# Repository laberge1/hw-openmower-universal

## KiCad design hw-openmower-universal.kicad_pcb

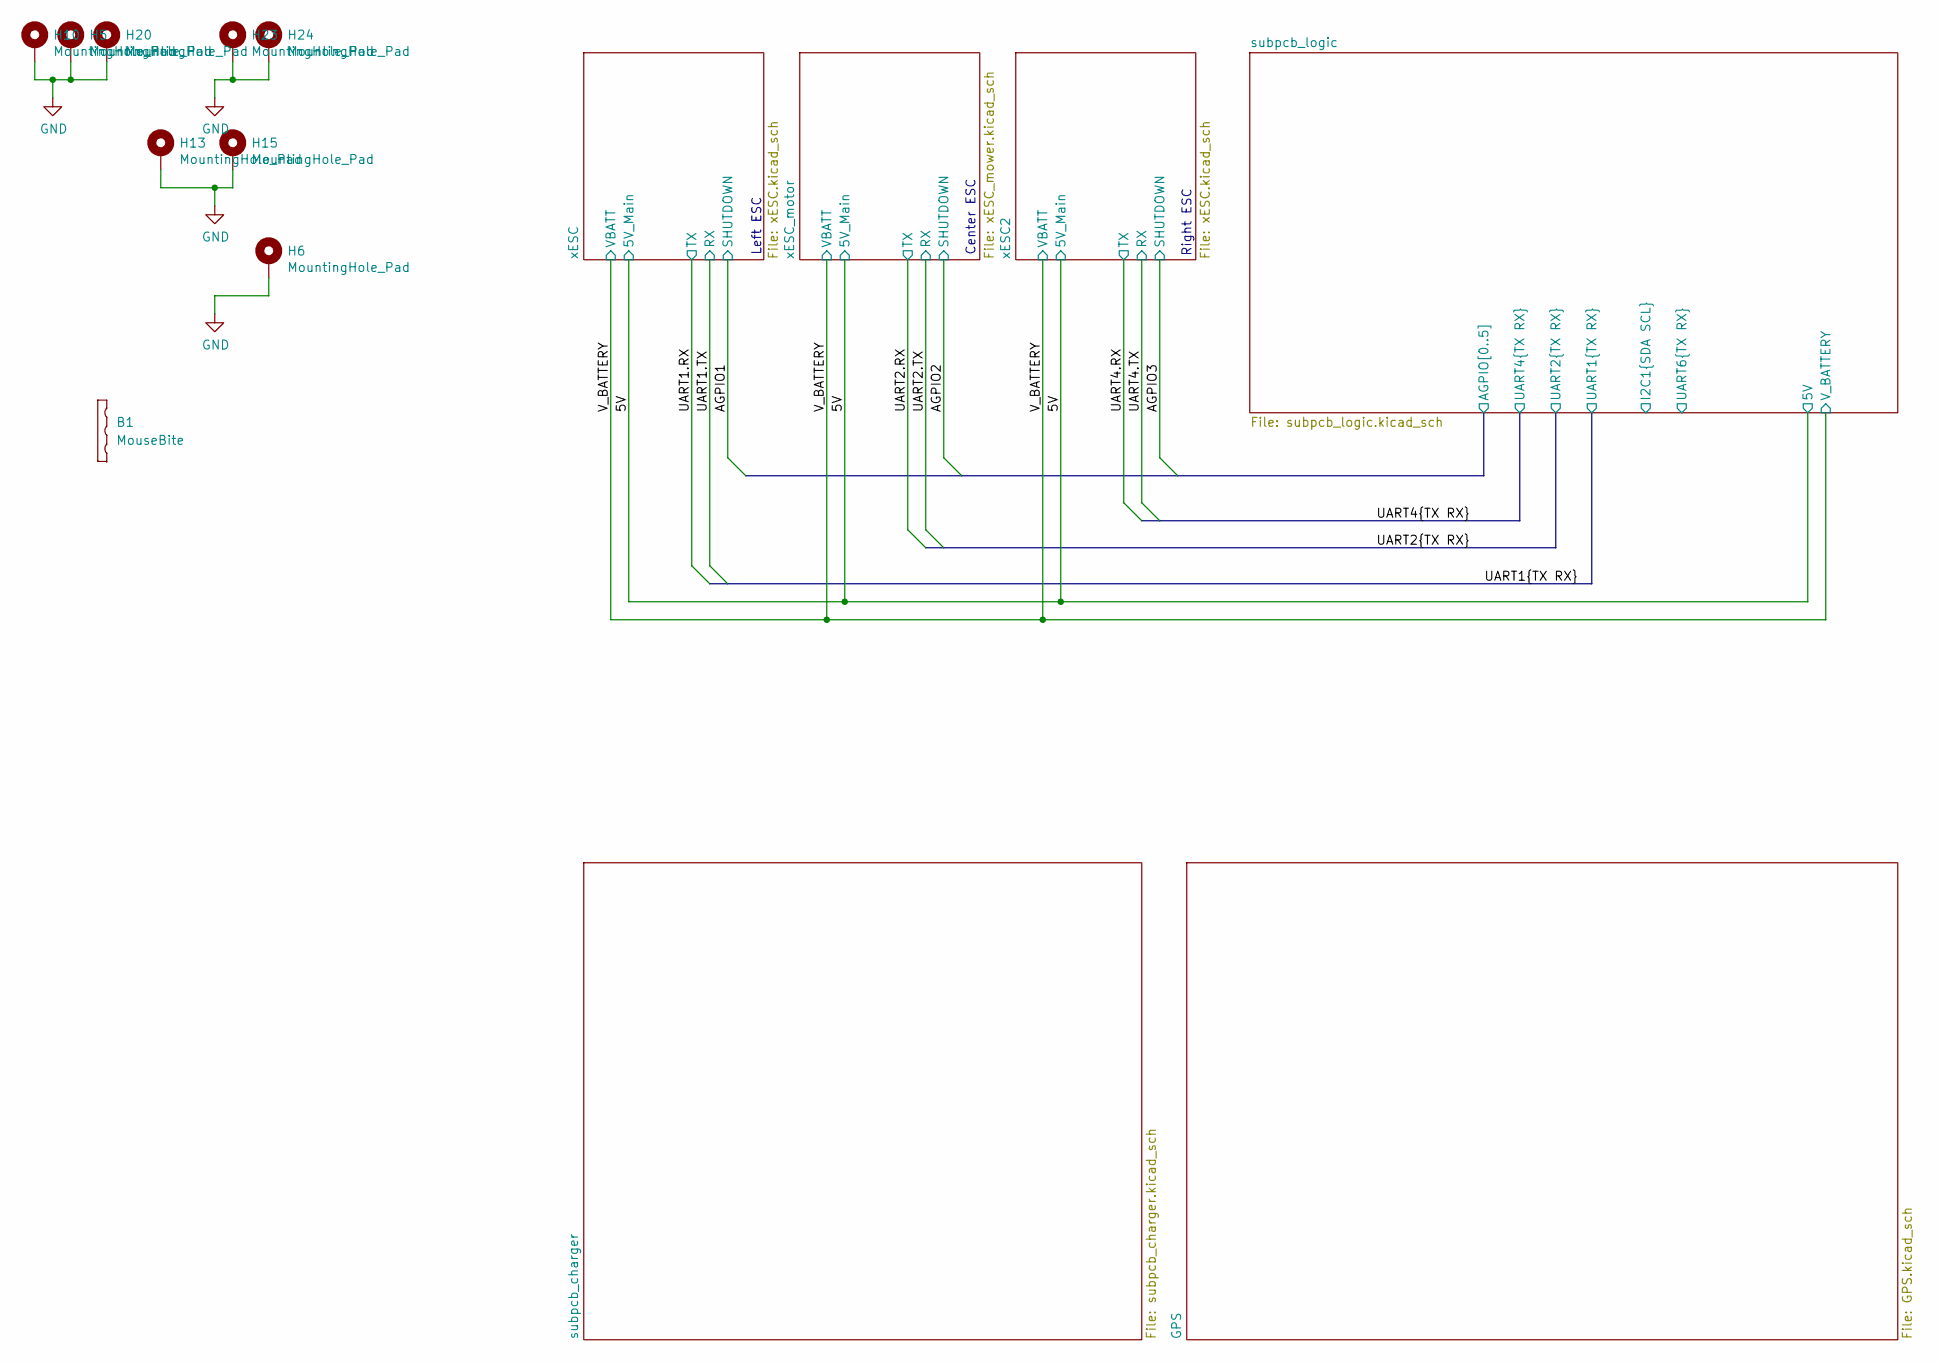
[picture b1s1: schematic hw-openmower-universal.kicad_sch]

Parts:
B1: MouseBite; MouseBite-Slot_2.0x2.0mm_outset_D0.5mm_P0.85mm_3h
H5, H6, H10, H13, H15, H20, H23, H24: MountingHole_Pad; MountingHole_4.3mm_M4_Pad_Via

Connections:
GND: H5.1, H6.1, H10.1, H13.1, H15.1, H20.1, H23.1, H24.1; also elsewhere on the board

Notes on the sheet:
Left ESC
Center ESC
Right ESC

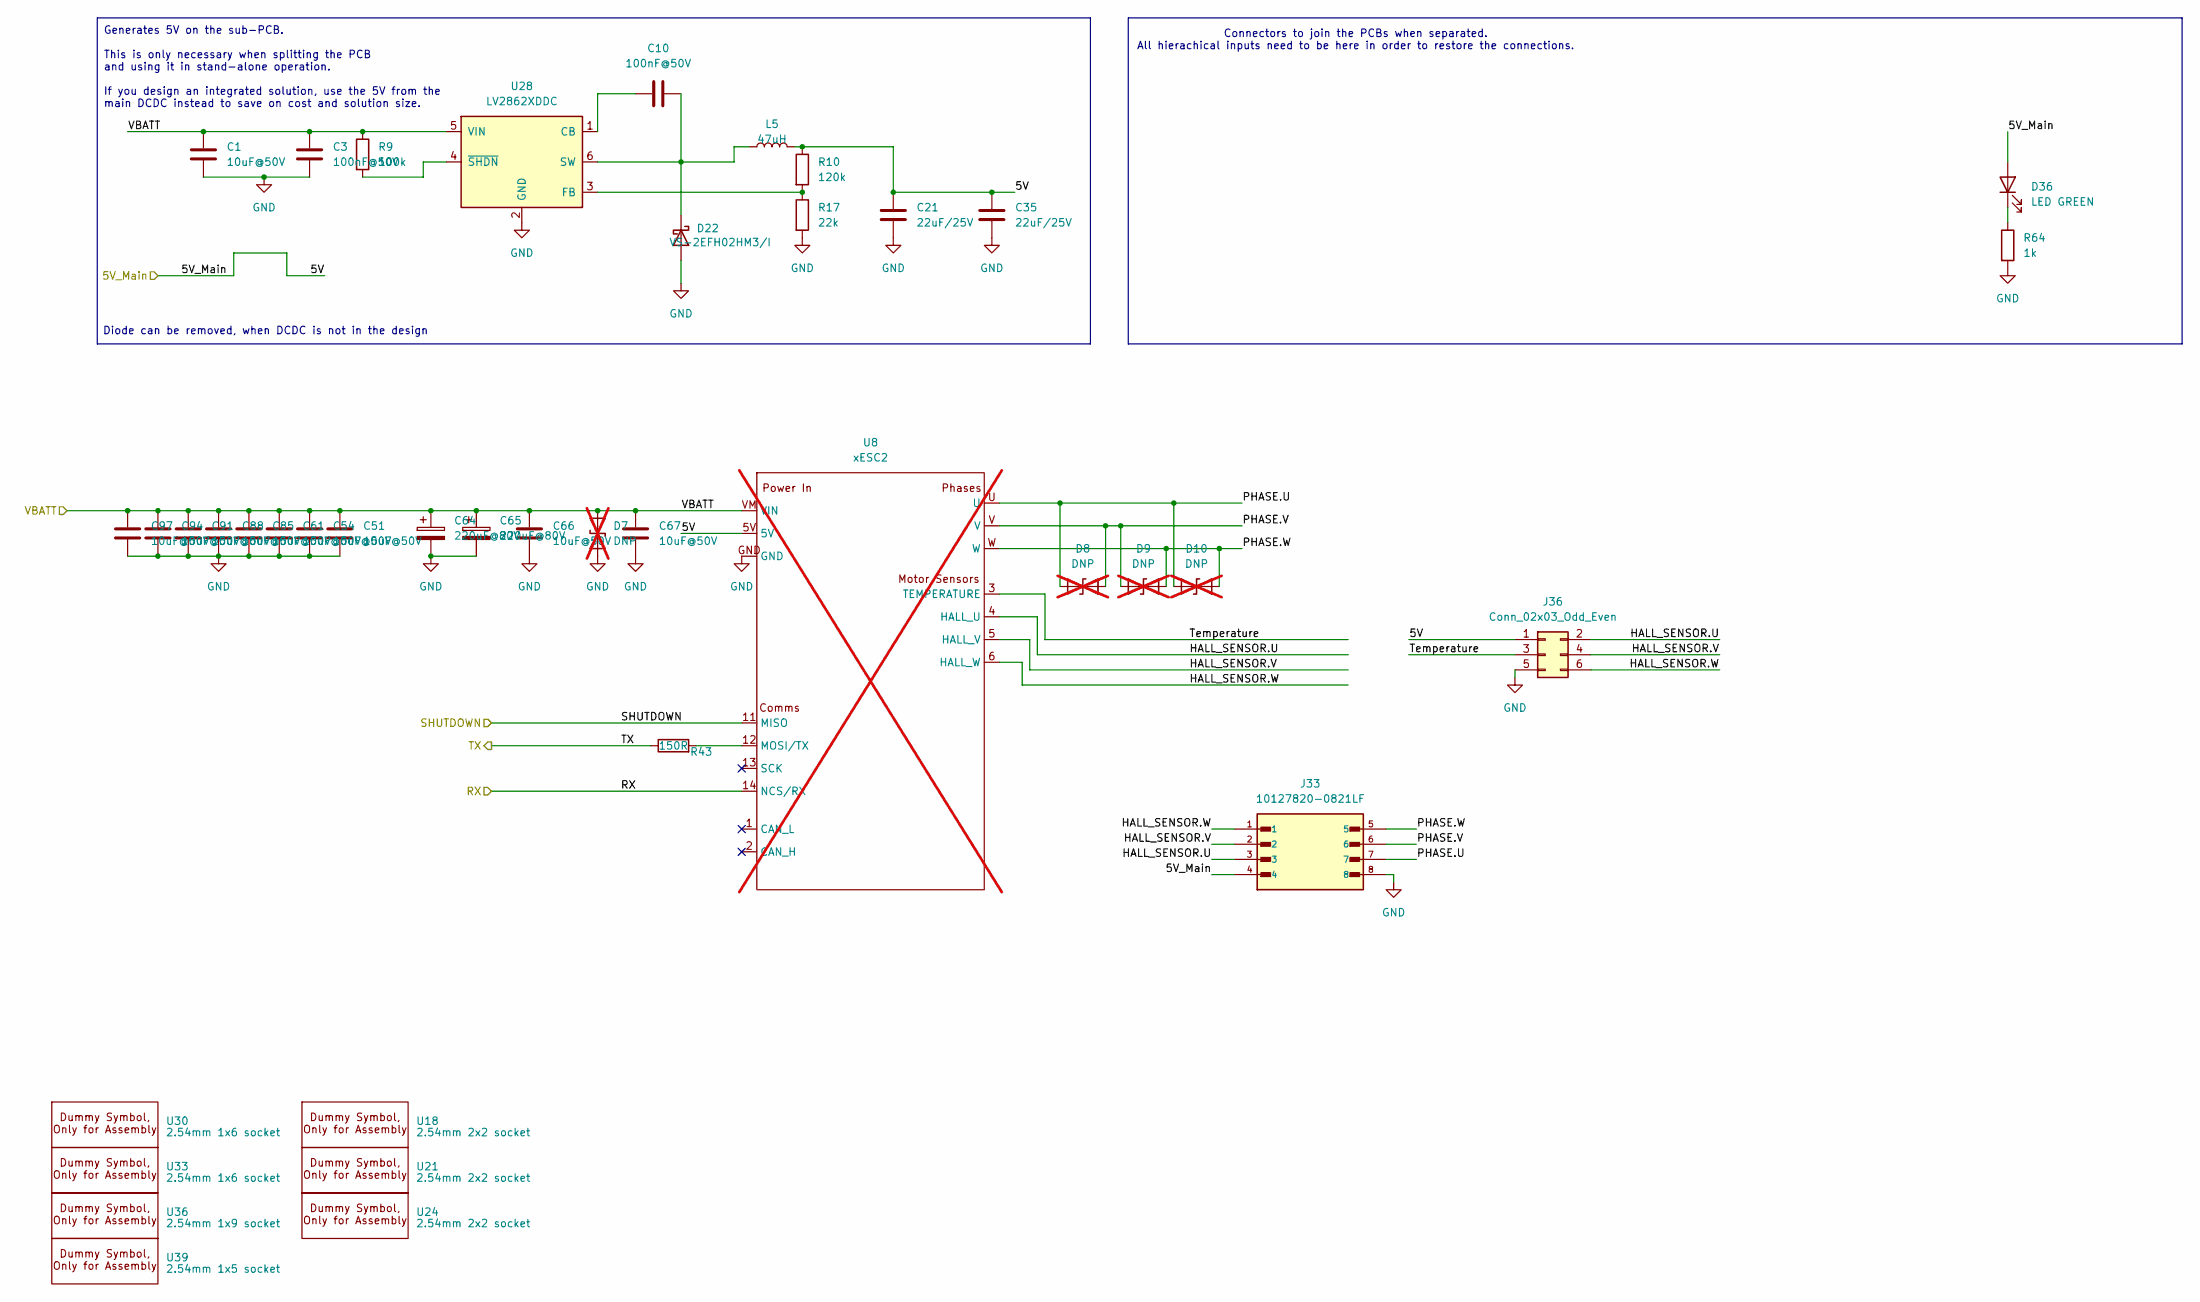
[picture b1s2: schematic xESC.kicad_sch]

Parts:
C1, C51, C54, C61, C66, C67, C85, C88, C91, C94, C97: 10uF@50V; C_1206_3216Metric; JLC C13585
C3, C10: 100nF@50V; C_0402_1005Metric; JLC C307331
C21, C35: 22uF/25V; C_0805_2012Metric; JLC C45783
C64, C65: 220uF@80V; CP_Radial_D10.0mm_P5.00mm; JLC C106516
D7: DNP; D_SMA; not fitted
D8, D9, D10: DNP; D_SMB; not fitted
D22: VS-2EFH02HM3/I; D_SMF; JLC C241868
D36: LED GREEN; LED_0805_2012Metric; JLC C2297
J33: 10127820-0821LF; AMPHENOL_10127820-0821LF; PARTREV R; DigikeyPN 609-10127820-0821LF-ND
J36: Conn_02x03_Odd_Even; PinHeader_2x03_P2.54mm_Vertical; JLC C5383104
L5: 47uH; L_Sunlord_SWPA5040S; JLC C86617
R9: 100k; R_0402_1005Metric; JLC C25741
R10: 120k; R_0603_1608Metric; JLC C25808
R17: 22k; R_0603_1608Metric; JLC C31850
R43: 150R; R_0603_1608Metric; JLC C22808
R64: 1k; R_0805_2012Metric; JLC C17513
U8: xESC2; xESC2-mini; not fitted
U18, U21, U24: 2.54mm 2x2 socket; Dummy; JLC C92273
U28: LV2862XDDC; SOT-23-6; JLC C3200285
U30, U33: 2.54mm 1x6 socket; Dummy; JLC C7509518
U36: 2.54mm 1x9 socket; Dummy; JLC C7509520
U39: 2.54mm 1x5 socket; Dummy; JLC C7509517

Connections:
/5V: C21.1, C35.1, D36.2 (A), J33.4, J36.1, L5.2, R10.1, U8.5V; also elsewhere on the board
/UART1.RX: R43.1; also elsewhere on the board
/UART1.TX: U8.14 (NCS/RX); also elsewhere on the board
/V_BATTERY: C1.1, C3.1, C51.1, C54.1, C61.1, C64.1, C65.1, C66.1, C67.1, C85.1, C88.1, C91.1, C94.1, C97.1, D7.2 (A2), R9.1, U8.VM (VIN), U28.5 (VIN); also elsewhere on the board
/subpcb_logic/AGPIO1: U8.11 (MISO); also elsewhere on the board
/xESC/HALL_SENSOR.U: J33.3, J36.2, U8.4 (HALL_U)
/xESC/HALL_SENSOR.V: J33.2, J36.4, U8.5 (HALL_V)
/xESC/HALL_SENSOR.W: J33.1, J36.6, U8.6 (HALL_W)
/xESC/PHASE.U: D8.2 (A2), D10.2 (A2), J33.7, U8.U
/xESC/PHASE.V: D8.1 (A1), D9.2 (A2), J33.6, U8.V
/xESC/PHASE.W: D9.1 (A1), D10.1 (A1), J33.5, U8.W
/xESC/Temperature: J36.3, U8.3 (TEMPERATURE)
GND: C1.2, C3.2, C21.2, C35.2, C51.2, C54.2, C61.2, C64.2, C65.2, C66.2, C67.2, C85.2, C88.2, C91.2, C94.2, C97.2, D7.1 (A1), D22.2 (A), J33.8, J36.5, R17.2, R64.2, U8.GND, U28.2 (GND); also elsewhere on the board
unnamed: C10.1, D22.1 (K), L5.1, U28.6 (SW)
unnamed: D36.1 (K), R64.1
unnamed: R43.2, U8.12 (MOSI/TX)
unnamed: C10.2, U28.1 (CB)
unnamed: R10.2, R17.1, U28.3 (FB)
unnamed: R9.2, U28.4 (~SHDN)

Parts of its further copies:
C53, C60, C74, C75, C77, C87, C90, C93, C96, C99, C104: 10uF@50V; C_1206_3216Metric; JLC C13585
C72, C73: 220uF@80V; CP_Radial_D10.0mm_P5.00mm; JLC C106516
C105, C106: 100nF@50V; C_0402_1005Metric; JLC C307331
C107, C108: 22uF/25V; C_0805_2012Metric; JLC C45783
D17: DNP; D_SMA; not fitted
D18, D19, D20: DNP; D_SMB; not fitted
D30: VS-2EFH02HM3/I; D_SMF; JLC C241868
D38: LED GREEN; LED_0805_2012Metric; JLC C2297
J38: Conn_02x03_Odd_Even; PinHeader_2x03_P2.54mm_Vertical; JLC C5383104
J46: 10127820-0821LF; AMPHENOL_10127820-0821LF; PARTREV R; DigikeyPN 609-10127820-0821LF-ND
L7: 47uH; L_Sunlord_SWPA5040S; JLC C86617
R30: 100k; R_0402_1005Metric; JLC C25741
R31: 120k; R_0603_1608Metric; JLC C25808
R32: 22k; R_0603_1608Metric; JLC C31850
R77: 150R; R_0603_1608Metric; JLC C22808
R78: 1k; R_0805_2012Metric; JLC C17513
U10: xESC2; xESC2-mini; not fitted
U20, U23, U26: 2.54mm 2x2 socket; Dummy; JLC C92273
U32, U35: 2.54mm 1x6 socket; Dummy; JLC C7509518
U38: 2.54mm 1x9 socket; Dummy; JLC C7509520
U41: 2.54mm 1x5 socket; Dummy; JLC C7509517
U47: LV2862XDDC; SOT-23-6; JLC C3200285

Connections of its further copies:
/5V: C107.1, C108.1, D38.2 (A), J38.1, J46.4, L7.2, R31.1, U10.5V; also elsewhere on the board
/UART4.RX: R77.1; also elsewhere on the board
/UART4.TX: U10.14 (NCS/RX); also elsewhere on the board
/V_BATTERY: C53.1, C60.1, C72.1, C73.1, C74.1, C75.1, C77.1, C87.1, C90.1, C93.1, C96.1, C99.1, C104.1, C105.1, D17.2 (A2), R30.1, U10.VM (VIN), U47.5 (VIN); also elsewhere on the board
/subpcb_logic/AGPIO3: U10.11 (MISO); also elsewhere on the board
/xESC2/HALL_SENSOR.U: J38.2, J46.3, U10.4 (HALL_U)
/xESC2/HALL_SENSOR.V: J38.4, J46.2, U10.5 (HALL_V)
/xESC2/HALL_SENSOR.W: J38.6, J46.1, U10.6 (HALL_W)
/xESC2/PHASE.U: D18.2 (A2), D20.2 (A2), J46.7, U10.U
/xESC2/PHASE.V: D18.1 (A1), D19.2 (A2), J46.6, U10.V
/xESC2/PHASE.W: D19.1 (A1), D20.1 (A1), J46.5, U10.W
/xESC2/Temperature: J38.3, U10.3 (TEMPERATURE)
GND: C53.2, C60.2, C72.2, C73.2, C74.2, C75.2, C77.2, C87.2, C90.2, C93.2, C96.2, C99.2, C104.2, C105.2, C107.2, C108.2, D17.1 (A1), D30.2 (A), J38.5, J46.8, R32.2, R78.2, U10.GND, U47.2 (GND); also elsewhere on the board
unnamed: C106.1, D30.1 (K), L7.1, U47.6 (SW)
unnamed: D38.1 (K), R78.1
unnamed: R77.2, U10.12 (MOSI/TX)
unnamed: C106.2, U47.1 (CB)
unnamed: R31.2, R32.1, U47.3 (FB)
unnamed: R30.2, U47.4 (~SHDN)

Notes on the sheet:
Diode can be removed, when DCDC is not in the design
Connectors to join the PCBs when separated. All hierachical inputs need to be here in order to restore the connections.
Generates 5V on the sub-PCB. This is only necessary when splitting the PCB and using it in stand-alone operation. If you design an integrated solution, use the 5V from the main DCDC instead to save on cost and solution size.

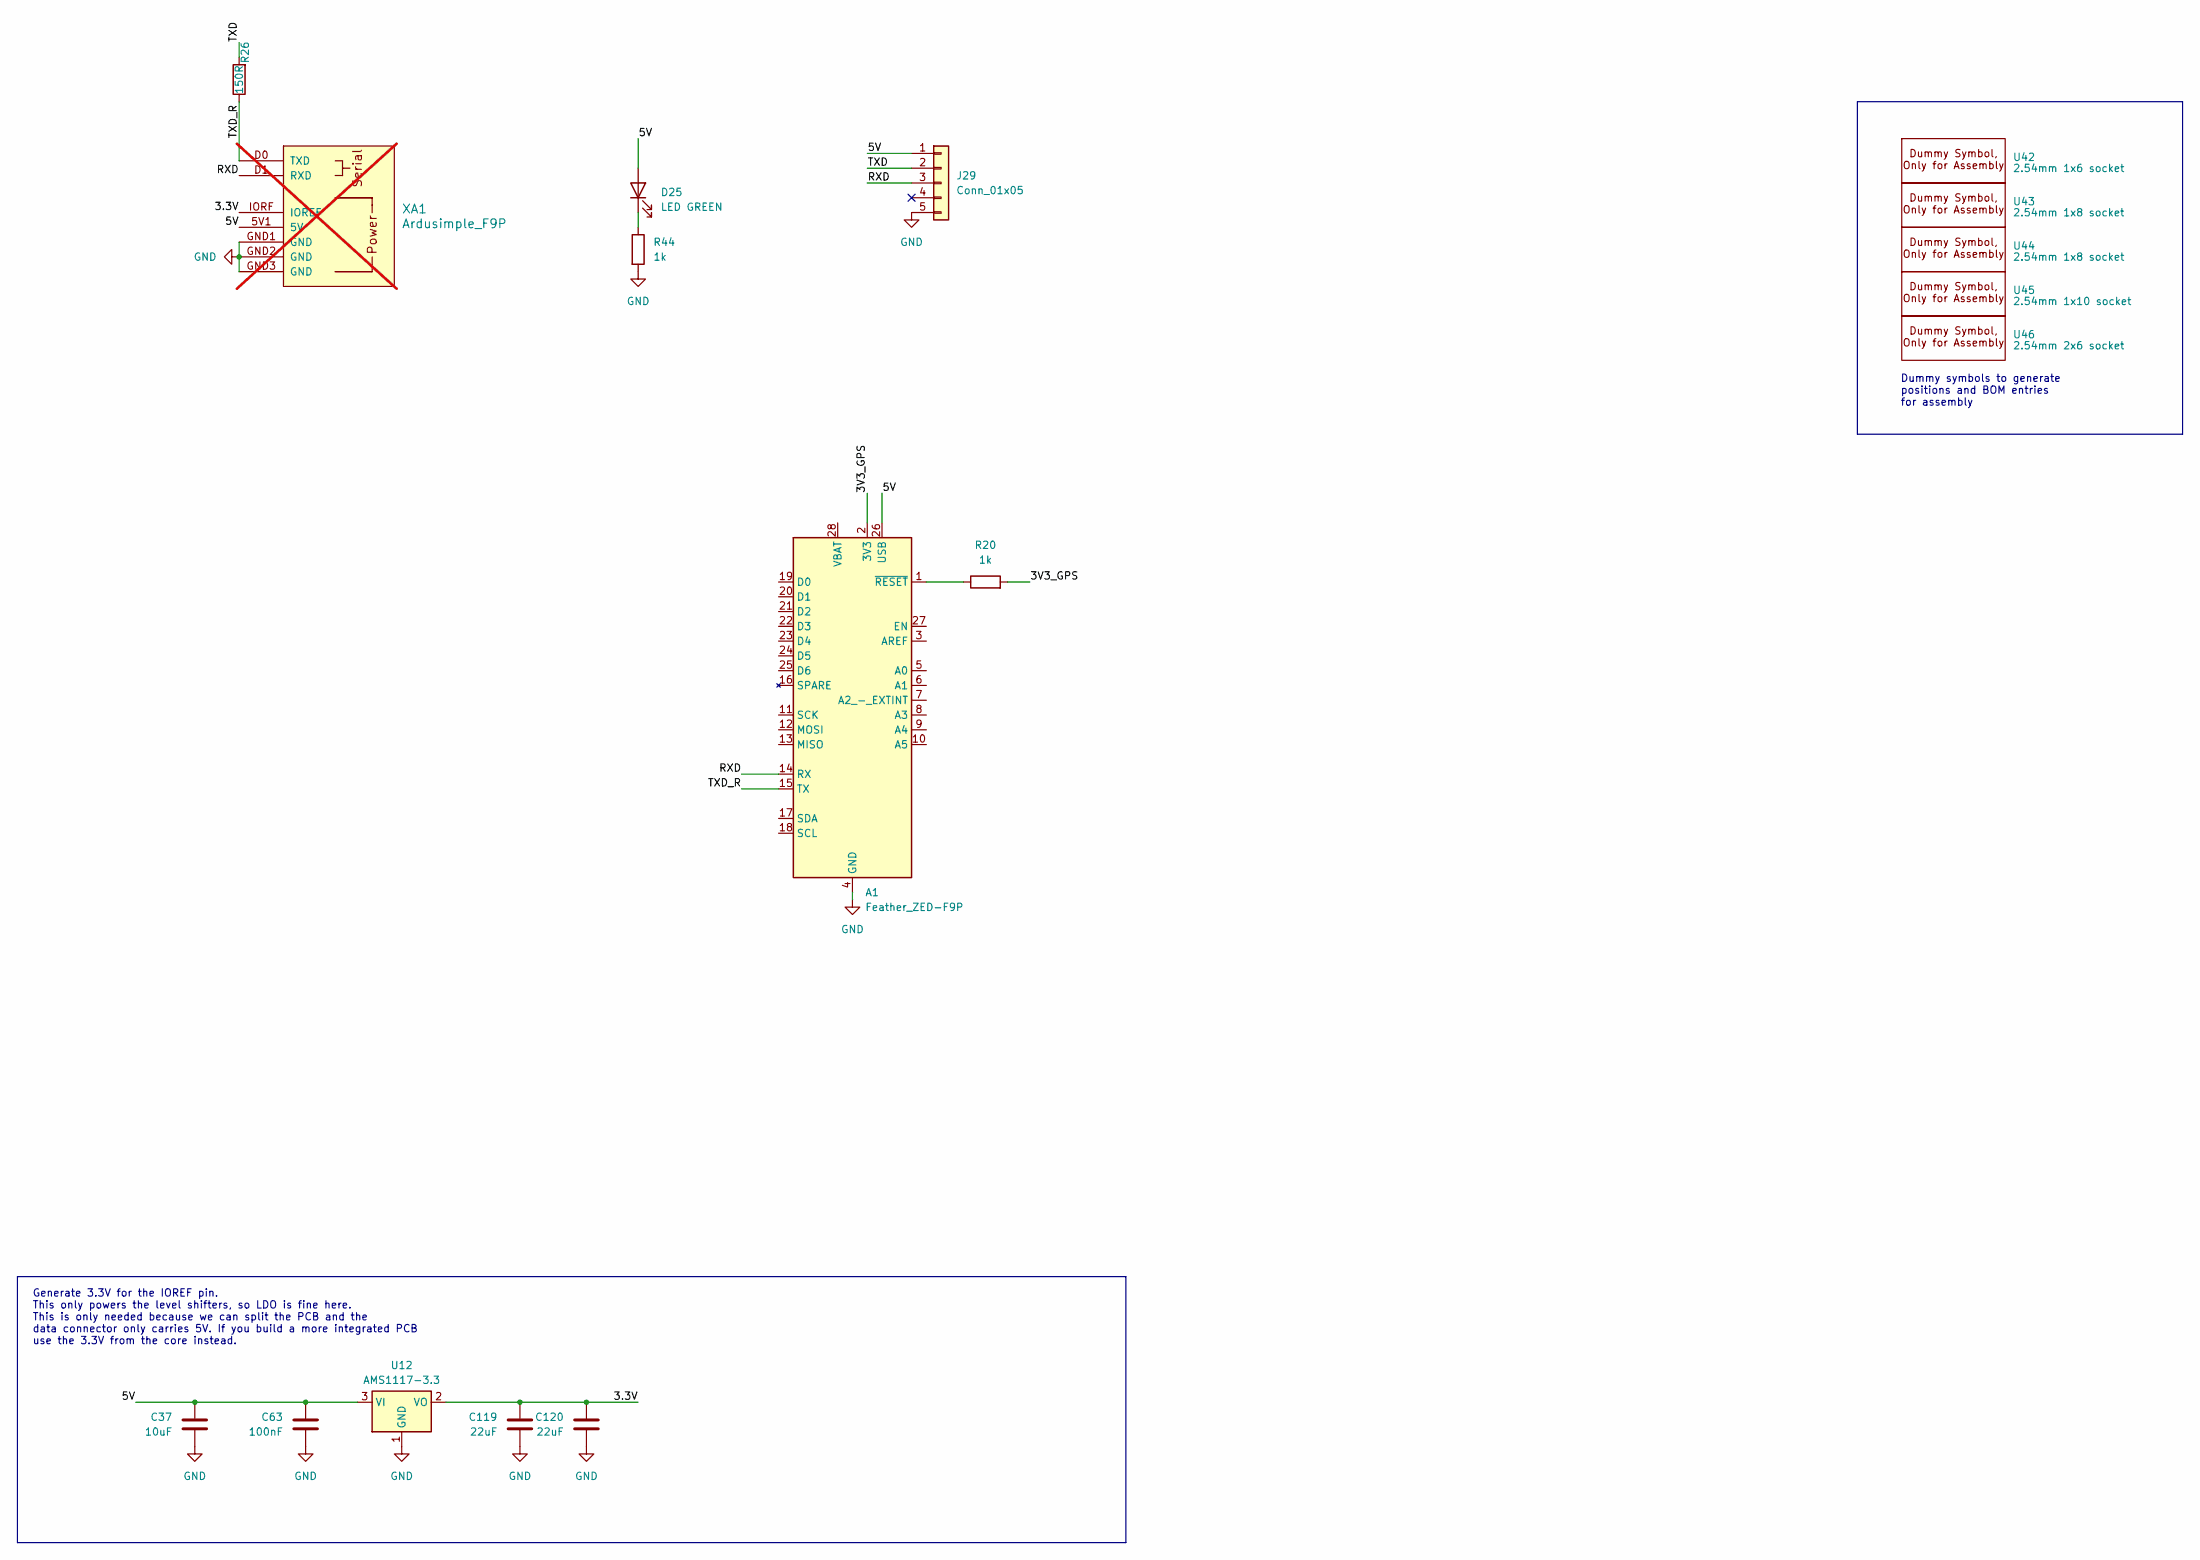
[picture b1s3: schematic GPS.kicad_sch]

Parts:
A1: Feather_ZED-F9P; Adafruit_Feather_WithMountingHoles
C37: 10uF; C_0402_1005Metric; JLC C15525
C63: 100nF; C_0402_1005Metric; JLC C307331
C119, C120: 22uF; C_0603_1608Metric; JLC C59461
D25: LED GREEN; LED_0805_2012Metric; JLC C2297
J29: Conn_01x05; JST_XH_B5B-XH-A_1x05_P2.50mm_Vertical; JLC C157991
R20, R44: 1k; R_0805_2012Metric; JLC C17513
R26: 150R; R_0603_1608Metric; JLC C22808
U12: AMS1117-3.3; SOT-223-3_TabPin2; JLC C6186
U42: 2.54mm 1x6 socket; Dummy; JLC C7509518
U43, U44: 2.54mm 1x8 socket; Dummy; JLC C7509515
U45: 2.54mm 1x10 socket; Dummy; JLC C7509514
U46: 2.54mm 2x6 socket; Dummy; JLC C718230
XA1: Ardusimple_F9P; Arduino_Uno_Shield_Ardusimple_Budget; not fitted

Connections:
/GPS/3.3V: C119.2, C120.2, U12.2 (VO), XA1.IORF (IOREF)
/GPS/3V3_GPS: A1.2 (3V3), R20.2
/GPS/5V: A1.26 (USB), C37.2, C63.2, D25.2 (A), J29.1, U12.3 (VI), XA1.5V1 (5V)
/GPS/RXD: A1.14 (RX), J29.3, XA1.D1 (RXD)
/GPS/TXD: J29.2, R26.2
/GPS/TXD_R: A1.15 (TX), R26.1, XA1.D0 (TXD)
GND: A1.4 (GND), C37.1, C63.1, C119.1, C120.1, J29.5, R44.2, U12.1 (GND), XA1.GND1 (GND), XA1.GND2 (GND), XA1.GND3 (GND); also elsewhere on the board
unnamed: A1.1 (~RESET), R20.1
unnamed: D25.1 (K), R44.1

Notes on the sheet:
Dummy symbols to generate positions and BOM entries for assembly
Generate 3.3V for the IOREF pin. This only powers the level shifters, so LDO is fine here. This is only needed because we can split the PCB and the data connector only carries 5V. If you build a more integrated PCB use the 3.3V from the core instead.

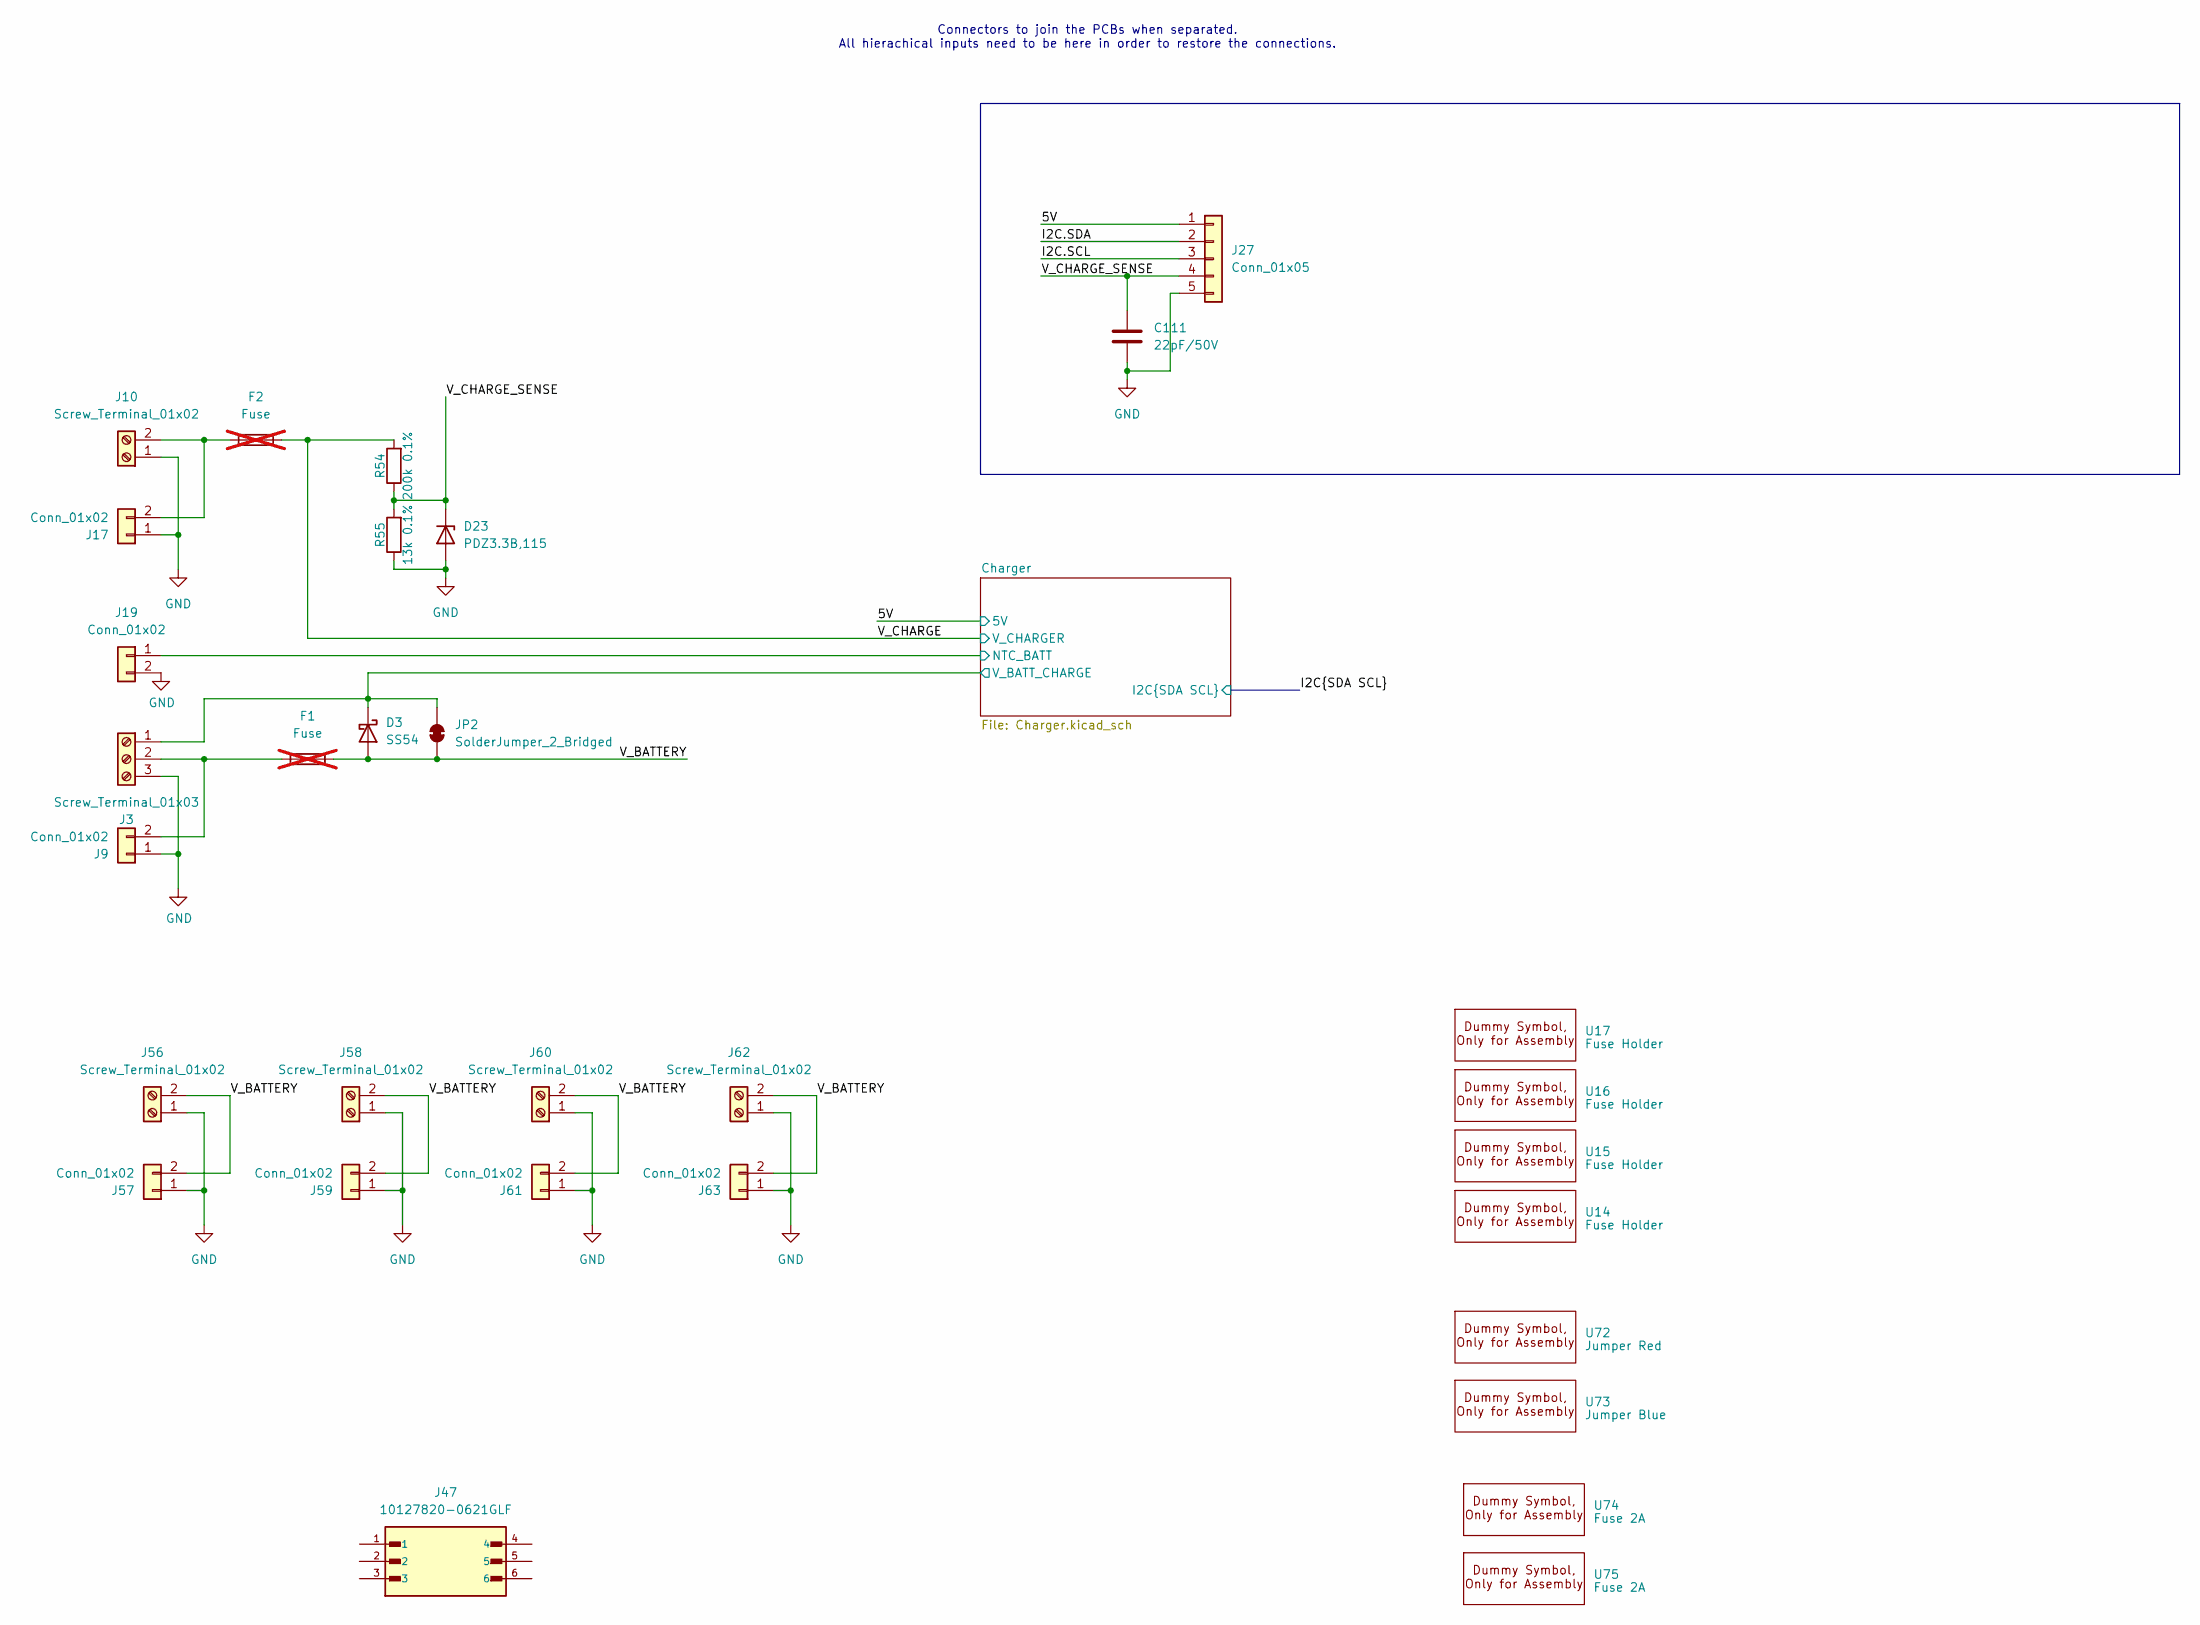
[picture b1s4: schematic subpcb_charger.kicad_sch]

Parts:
C111: 22pF/50V; C_0603_1608Metric; JLC C1653
D3: SS54; D_SMA; Part Number SB54AFC_R1_00001; Digikey 3757-SB54AFC_R1_00001CT-ND
D23: PDZ3.3B,115; D_SOD-323; JLC C426855
F1, F2: Fuse; Fuseholder5x20_horiz_open_inline_Type-I; not fitted
J3: Screw_Terminal_01x03; TerminalBlock_Phoenix_MKDS-1,5-3-5.08_1x03_P5.08mm_Horizont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; JLC C557666
J9, J17: Conn_01x02; AMASS_XT30U-M_1x02_P5.0mm_Vertical; JLC C99101
J10, J56, J58, J60, J62: Screw_Terminal_01x02; TerminalBlock_Phoenix_MKDS-1,5-2-5.08_1x02_P5.08mm_Horizont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; JLC C557665
J19: Conn_01x02; JST_XH_B2B-XH-A_1x02_P2.50mm_Vertical; JLC C2910525
J27: Conn_01x05; JST_XH_B5B-XH-A_1x05_P2.50mm_Vertical; JLC C157991
J47: 10127820-0621GLF; AMPHENOL_10127820-0621GLF; PARTREV R; Digikey PN 609-10127820-0621GLF-ND
J57, J59, J61, J63: Conn_01x02; AMASS_XT30U-F_1x02_P5.0mm_Vertical; JLC C99102
JP2: SolderJumper_2_Bridged; SolderJumper-2_P1.3mm_Bridged2Bar_Pad1.0x1.5mm
R54: 200k 0.1%; R_0402_1005Metric; JLC C728556
R55: 13k 0.1%; R_0402_1005Metric; JLC C852524
U14, U15, U16, U17: Fuse Holder; Dummy; JLC C3130
U72: Jumper Red; Dummy; JLC C20417889
U73: Jumper Blue; Dummy; JLC C20417886
U74, U75: Fuse 2A; Dummy; JLC C356459

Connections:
/subpcb_charger/5V: J27.1; also elsewhere on the board
/subpcb_charger/Charger/V_BATT_CHARGE: D3.1 (K), J3.1, JP2.2 (B); also elsewhere on the board
/subpcb_charger/I2C.SCL: J27.3; also elsewhere on the board
/subpcb_charger/I2C.SDA: J27.2; also elsewhere on the board
/subpcb_charger/NTC_BATT: J19.1, J47.5; also elsewhere on the board
/subpcb_charger/V_BATTERY: D3.2 (A), F1.2, J56.2, J57.2, J58.2, J59.2, J60.2, J61.2, J62.2, J63.2, JP2.1 (A)
/subpcb_charger/V_CHARGE: F2.2, R54.2; also elsewhere on the board
/subpcb_charger/V_CHARGE_SENSE: C111.1, D23.1 (K), J27.4, R54.1, R55.2
GND: C111.2, D23.2 (A), J3.3, J9.1, J10.1, J17.1, J19.2, J27.5, J47.1, J47.2, J47.6, J56.1, J57.1, J58.1, J59.1, J60.1, J61.1, J62.1, J63.1, R55.1; also elsewhere on the board

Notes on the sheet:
Connectors to join the PCBs when separated. All hierachical inputs need to be here in order to restore the connections.

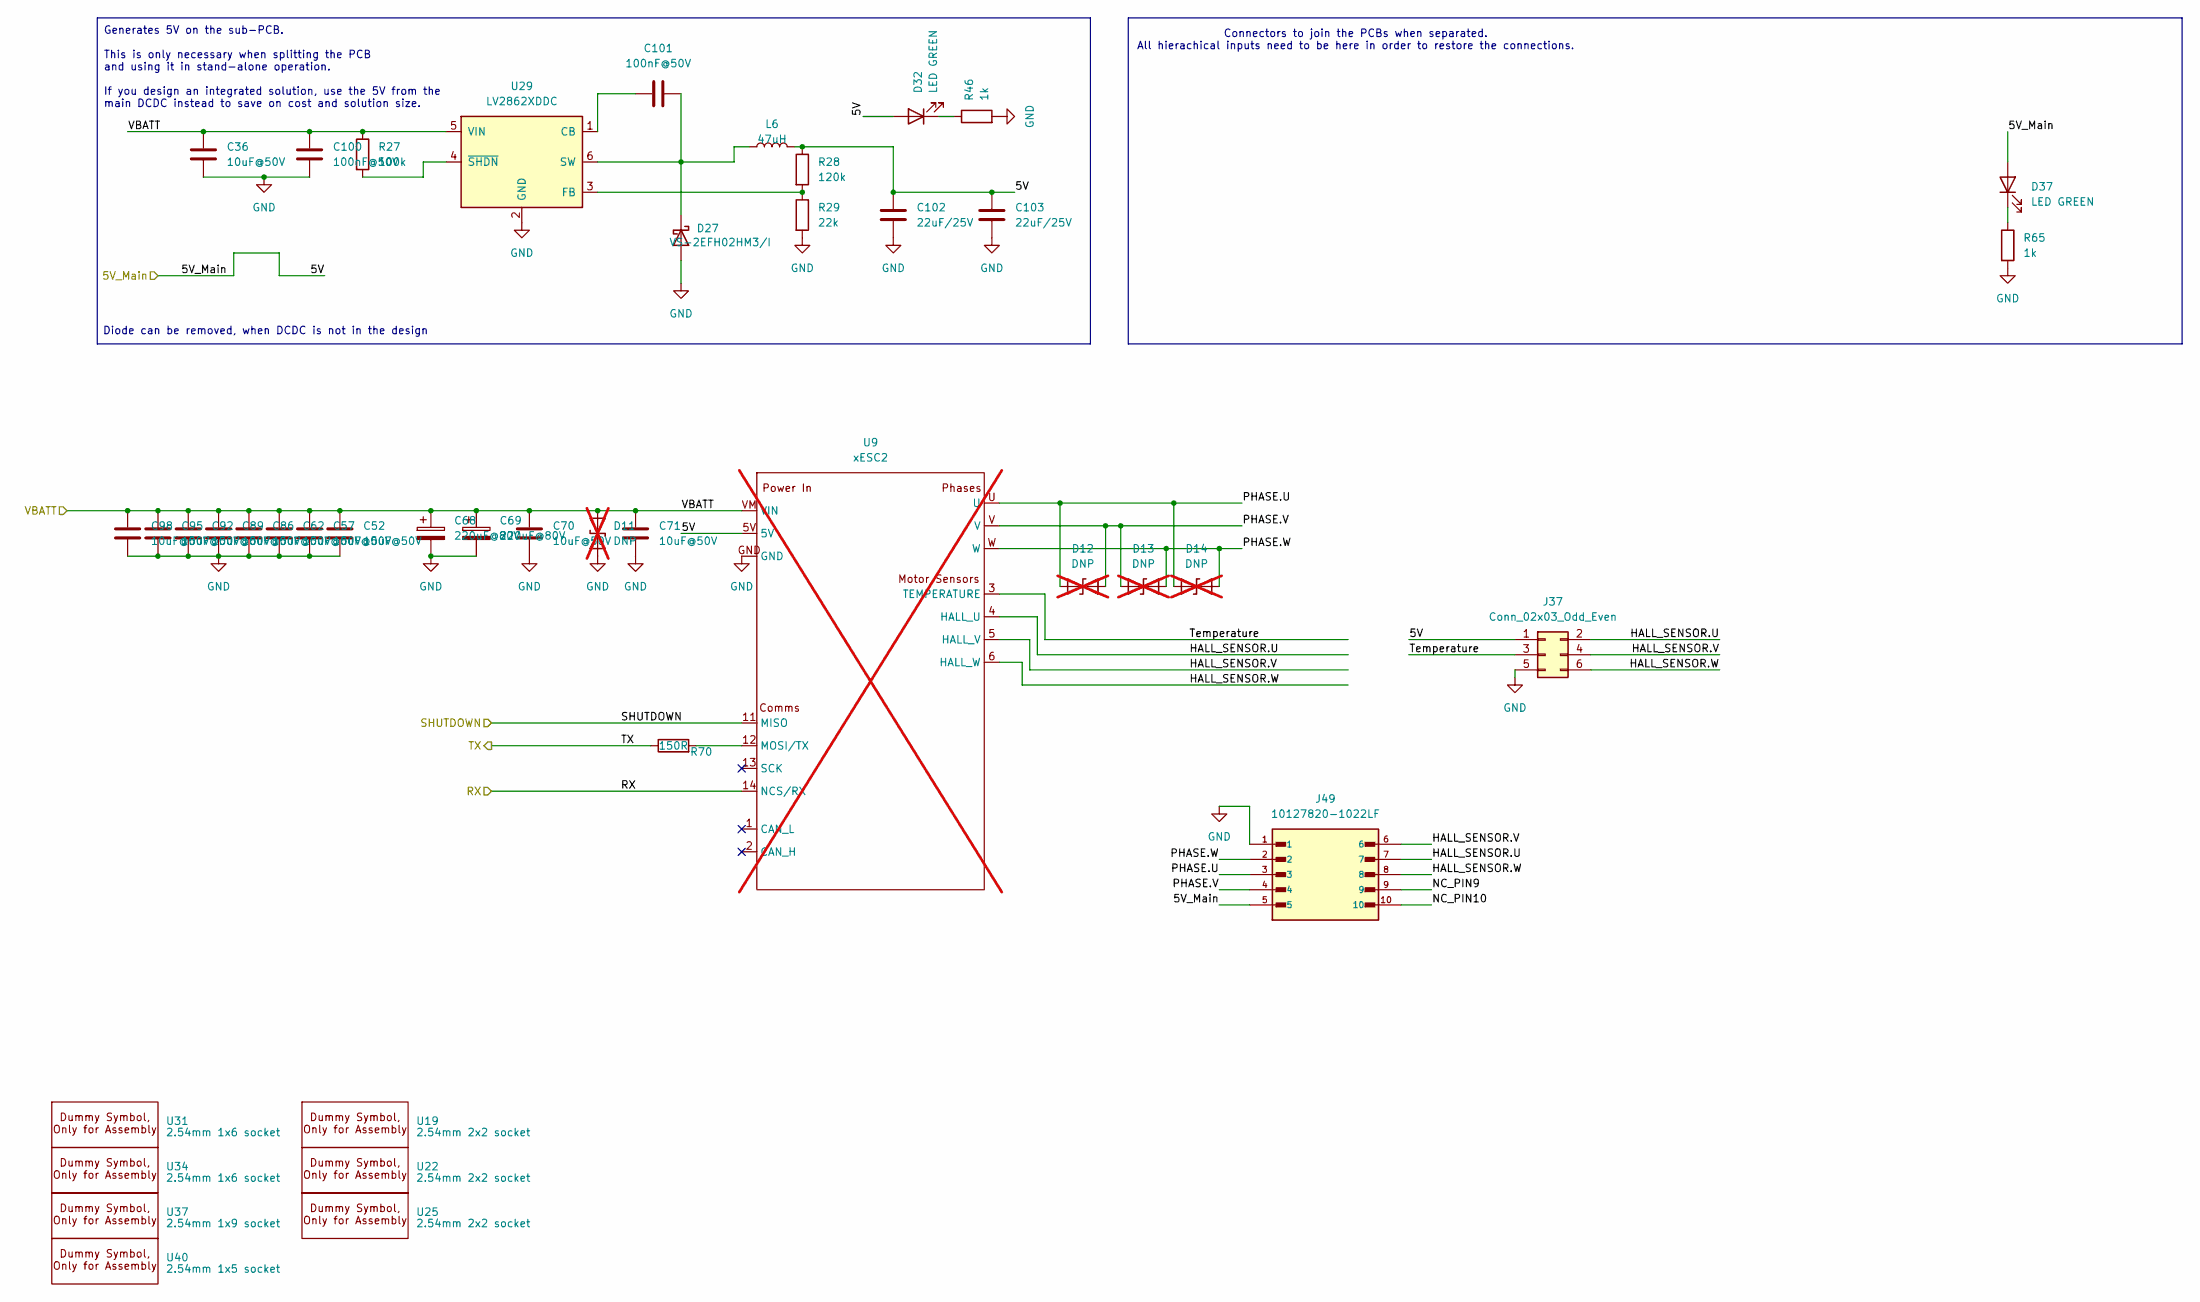
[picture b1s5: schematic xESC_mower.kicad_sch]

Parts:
C36, C52, C57, C62, C70, C71, C86, C89, C92, C95, C98: 10uF@50V; C_1206_3216Metric; JLC C13585
C68, C69: 220uF@80V; CP_Radial_D10.0mm_P5.00mm; JLC C106516
C100, C101: 100nF@50V; C_0402_1005Metric; JLC C307331
C102, C103: 22uF/25V; C_0805_2012Metric; JLC C45783
D11: DNP; D_SMA; not fitted
D12, D13, D14: DNP; D_SMB; not fitted
D27: VS-2EFH02HM3/I; D_SMF; JLC C241868
D32, D37: LED GREEN; LED_0805_2012Metric; JLC C2297
J37: Conn_02x03_Odd_Even; PinHeader_2x03_P2.54mm_Vertical; JLC C5383104
J49: 10127820-1022LF; AMPHENOL_10127820-1022LF; PARTREV R; Digikey PN 609-4876-ND
L6: 47uH; L_Sunlord_SWPA5040S; JLC C86617
R27: 100k; R_0402_1005Metric; JLC C25741
R28: 120k; R_0603_1608Metric; JLC C25808
R29: 22k; R_0603_1608Metric; JLC C31850
R46, R65: 1k; R_0805_2012Metric; JLC C17513
R70: 150R; R_0603_1608Metric; JLC C22808
U9: xESC2; xESC2-mini; not fitted
U19, U22, U25: 2.54mm 2x2 socket; Dummy; JLC C92273
U29: LV2862XDDC; SOT-23-6; JLC C3200285
U31, U34: 2.54mm 1x6 socket; Dummy; JLC C7509518
U37: 2.54mm 1x9 socket; Dummy; JLC C7509520
U40: 2.54mm 1x5 socket; Dummy; JLC C7509517

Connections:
/5V: C102.1, C103.1, D32.2 (A), D37.2 (A), J37.1, J49.5, L6.2, R28.1, U9.5V; also elsewhere on the board
/UART2.RX: R70.1; also elsewhere on the board
/UART2.TX: U9.14 (NCS/RX); also elsewhere on the board
/V_BATTERY: C36.1, C52.1, C57.1, C62.1, C68.1, C69.1, C70.1, C71.1, C86.1, C89.1, C92.1, C95.1, C98.1, C100.1, D11.2 (A2), R27.1, U9.VM (VIN), U29.5 (VIN); also elsewhere on the board
/subpcb_logic/AGPIO2: U9.11 (MISO); also elsewhere on the board
/xESC_motor/HALL_SENSOR.U: J37.2, J49.7, U9.4 (HALL_U)
/xESC_motor/HALL_SENSOR.V: J37.4, J49.6, U9.5 (HALL_V)
/xESC_motor/HALL_SENSOR.W: J37.6, J49.8, U9.6 (HALL_W)
/xESC_motor/NC_PIN9: J49.9
/xESC_motor/NC_PIN10: J49.10
/xESC_motor/PHASE.U: D12.2 (A2), D14.2 (A2), J49.3, U9.U
/xESC_motor/PHASE.V: D12.1 (A1), D13.2 (A2), J49.4, U9.V
/xESC_motor/PHASE.W: D13.1 (A1), D14.1 (A1), J49.2, U9.W
/xESC_motor/Temperature: J37.3, U9.3 (TEMPERATURE)
GND: C36.2, C52.2, C57.2, C62.2, C68.2, C69.2, C70.2, C71.2, C86.2, C89.2, C92.2, C95.2, C98.2, C100.2, C102.2, C103.2, D11.1 (A1), D27.2 (A), J37.5, J49.1, R29.2, R46.2, R65.2, U9.GND, U29.2 (GND); also elsewhere on the board
unnamed: C101.1, D27.1 (K), L6.1, U29.6 (SW)
unnamed: D32.1 (K), R46.1
unnamed: D37.1 (K), R65.1
unnamed: R70.2, U9.12 (MOSI/TX)
unnamed: C101.2, U29.1 (CB)
unnamed: R28.2, R29.1, U29.3 (FB)
unnamed: R27.2, U29.4 (~SHDN)

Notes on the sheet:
Diode can be removed, when DCDC is not in the design
Connectors to join the PCBs when separated. All hierachical inputs need to be here in order to restore the connections.
Generates 5V on the sub-PCB. This is only necessary when splitting the PCB and using it in stand-alone operation. If you design an integrated solution, use the 5V from the main DCDC instead to save on cost and solution size.

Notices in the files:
hw-openmower-universal.kicad_pcb:
License CC BY 4.0
